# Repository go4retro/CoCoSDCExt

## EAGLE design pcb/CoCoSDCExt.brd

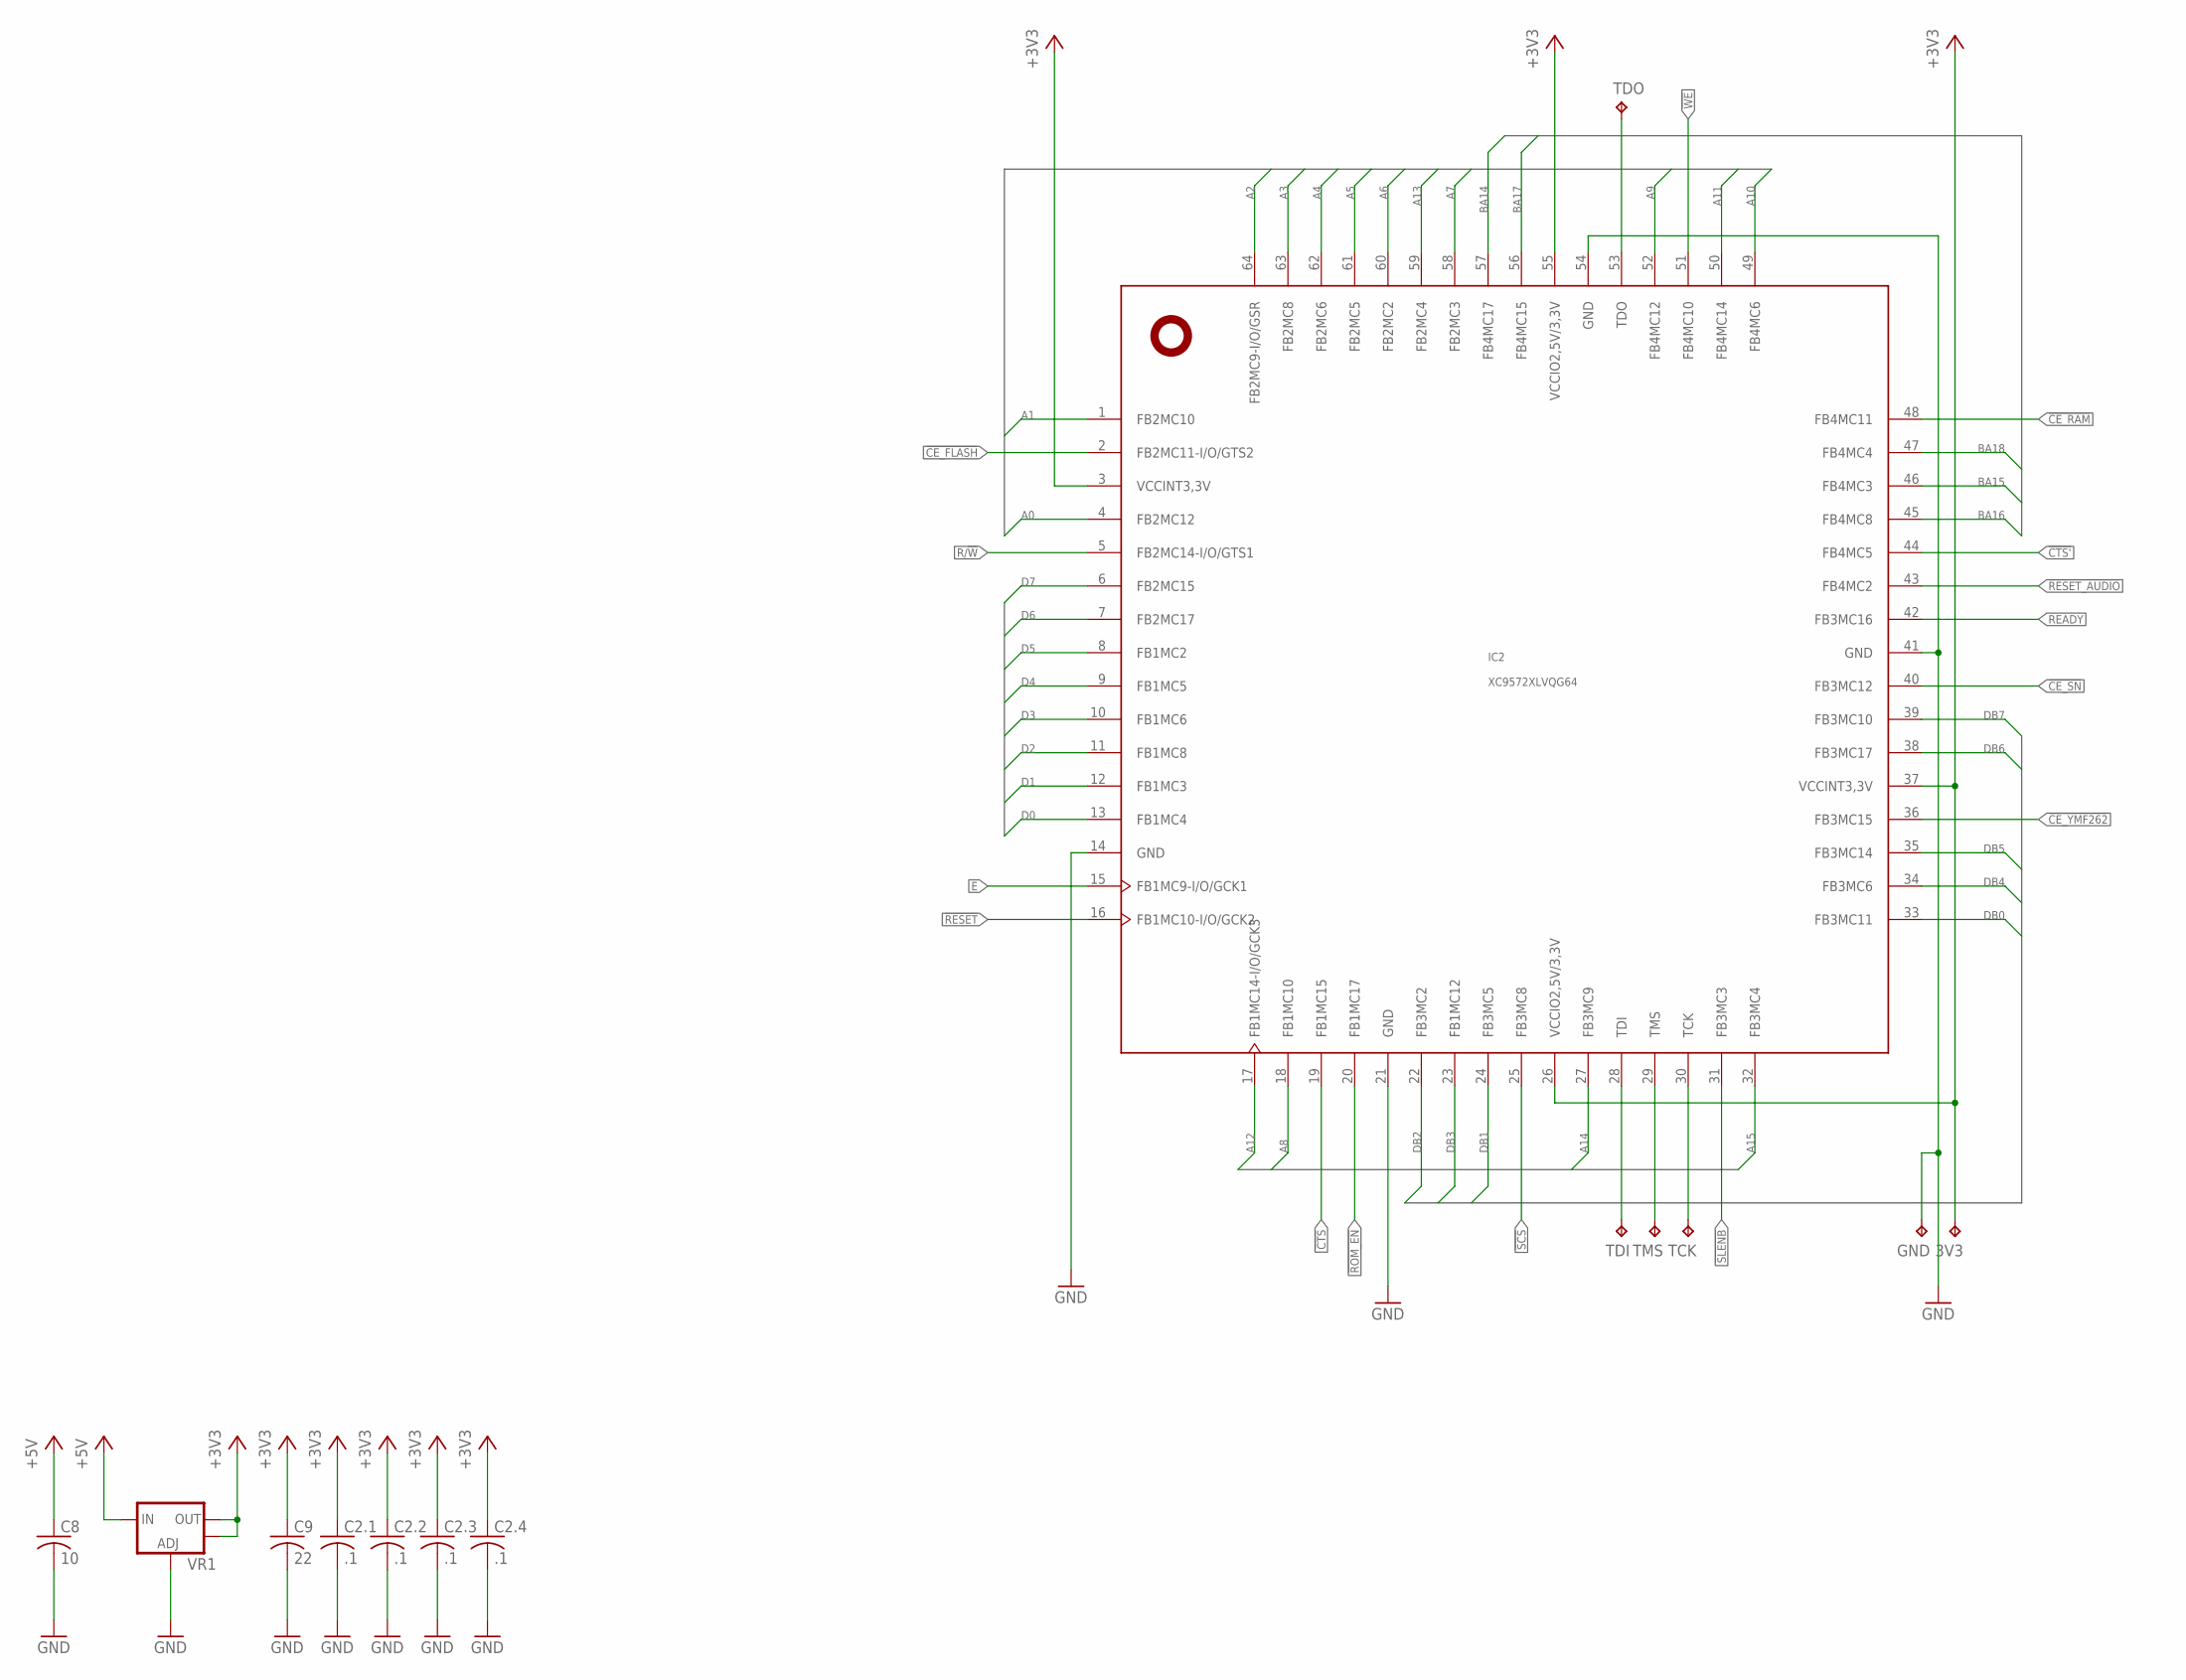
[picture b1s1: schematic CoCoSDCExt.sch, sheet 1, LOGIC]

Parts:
3V3: TPTP08R; TP08R
C2.1, C2.2, C2.3, C2.4: .1; C0402
C8: 10; C0805
C9: 22; C0805
GND: TPTP08R; TP08R
IC2: XC9572XLVQG64; VQFP64
TCK: TPTP08R; TP08R
TDI: TPTP08R; TP08R
TDO: TPTP08R; TP08R
TMS: TPTP08R; TP08R
VR1: V_REG_LM1117SOT223; SOT223

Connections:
!CE_FLASH: IC2.2 (FB2MC11-I/O/GTS2); also elsewhere on the board
!CE_RAM: IC2.48 (FB4MC11); also elsewhere on the board
!CE_SN: IC2.40 (FB3MC12); also elsewhere on the board
!CE_YMF262: IC2.36 (FB3MC15); also elsewhere on the board
!CTS: IC2.19 (FB1MC15); also elsewhere on the board
!CTS': IC2.44 (FB4MC5); also elsewhere on the board
!RESET: IC2.16 (FB1MC10-I/O/GCK2); also elsewhere on the board
!RESET_AUDIO: IC2.43 (FB4MC2); also elsewhere on the board
!ROM_EN: IC2.20 (FB1MC17); also elsewhere on the board
!SCS: IC2.25 (FB3MC8); also elsewhere on the board
!SLENB: IC2.31 (FB3MC3); also elsewhere on the board
!WE: IC2.51 (FB4MC10); also elsewhere on the board
+3V3: 3V3.TP, C2.1.1, C2.2.1, C2.3.1, C2.4.1, C9.1, IC2.3 (VCCINT3,3V), IC2.26 (VCCIO2,5V/3,3V), IC2.37 (VCCINT3,3V), IC2.55 (VCCIO2,5V/3,3V), VR1.2 (OUT), VR1.4 (OUT); also elsewhere on the board
+5V: C8.1, VR1.3 (IN); also elsewhere on the board
A0: IC2.4 (FB2MC12); also elsewhere on the board
A1: IC2.1 (FB2MC10); also elsewhere on the board
A2: IC2.64 (FB2MC9-I/O/GSR); also elsewhere on the board
A3: IC2.63 (FB2MC8); also elsewhere on the board
A4: IC2.62 (FB2MC6); also elsewhere on the board
A5: IC2.61 (FB2MC5); also elsewhere on the board
A6: IC2.60 (FB2MC2); also elsewhere on the board
A7: IC2.58 (FB2MC3); also elsewhere on the board
A8: IC2.18 (FB1MC10); also elsewhere on the board
A9: IC2.52 (FB4MC12); also elsewhere on the board
A10: IC2.49 (FB4MC6); also elsewhere on the board
A11: IC2.50 (FB4MC14); also elsewhere on the board
A12: IC2.17 (FB1MC14-I/O/GCK3); also elsewhere on the board
A13: IC2.59 (FB2MC4); also elsewhere on the board
A14: IC2.27 (FB3MC9); also elsewhere on the board
A15: IC2.32 (FB3MC4); also elsewhere on the board
BA14: IC2.57 (FB4MC17); also elsewhere on the board
BA15: IC2.46 (FB4MC3); also elsewhere on the board
BA16: IC2.45 (FB4MC8); also elsewhere on the board
BA17: IC2.56 (FB4MC15); also elsewhere on the board
BA18: IC2.47 (FB4MC4); also elsewhere on the board
D0: IC2.13 (FB1MC4); also elsewhere on the board
D1: IC2.12 (FB1MC3); also elsewhere on the board
D2: IC2.11 (FB1MC8); also elsewhere on the board
D3: IC2.10 (FB1MC6); also elsewhere on the board
D4: IC2.9 (FB1MC5); also elsewhere on the board
D5: IC2.8 (FB1MC2); also elsewhere on the board
D6: IC2.7 (FB2MC17); also elsewhere on the board
D7: IC2.6 (FB2MC15); also elsewhere on the board
DB0: IC2.33 (FB3MC11); also elsewhere on the board
DB1: IC2.24 (FB3MC5); also elsewhere on the board
DB2: IC2.22 (FB3MC2); also elsewhere on the board
DB3: IC2.23 (FB1MC12); also elsewhere on the board
DB4: IC2.34 (FB3MC6); also elsewhere on the board
DB5: IC2.35 (FB3MC14); also elsewhere on the board
DB6: IC2.38 (FB3MC17); also elsewhere on the board
DB7: IC2.39 (FB3MC10); also elsewhere on the board
E: IC2.15 (FB1MC9-I/O/GCK1); also elsewhere on the board
GND: C2.1.2, C2.2.2, C2.3.2, C2.4.2, C8.2, C9.2, GND.TP, IC2.14 (GND), IC2.21 (GND), IC2.41 (GND), IC2.54 (GND), VR1.1 (ADJ); also elsewhere on the board
R/!W: IC2.5 (FB2MC14-I/O/GTS1); also elsewhere on the board
READY: IC2.42 (FB3MC16); also elsewhere on the board
TCK: IC2.30 (TCK), TCK.TP
TDI: IC2.28 (TDI), TDI.TP
TDO: IC2.53 (TDO), TDO.TP
TMS: IC2.29 (TMS), TMS.TP

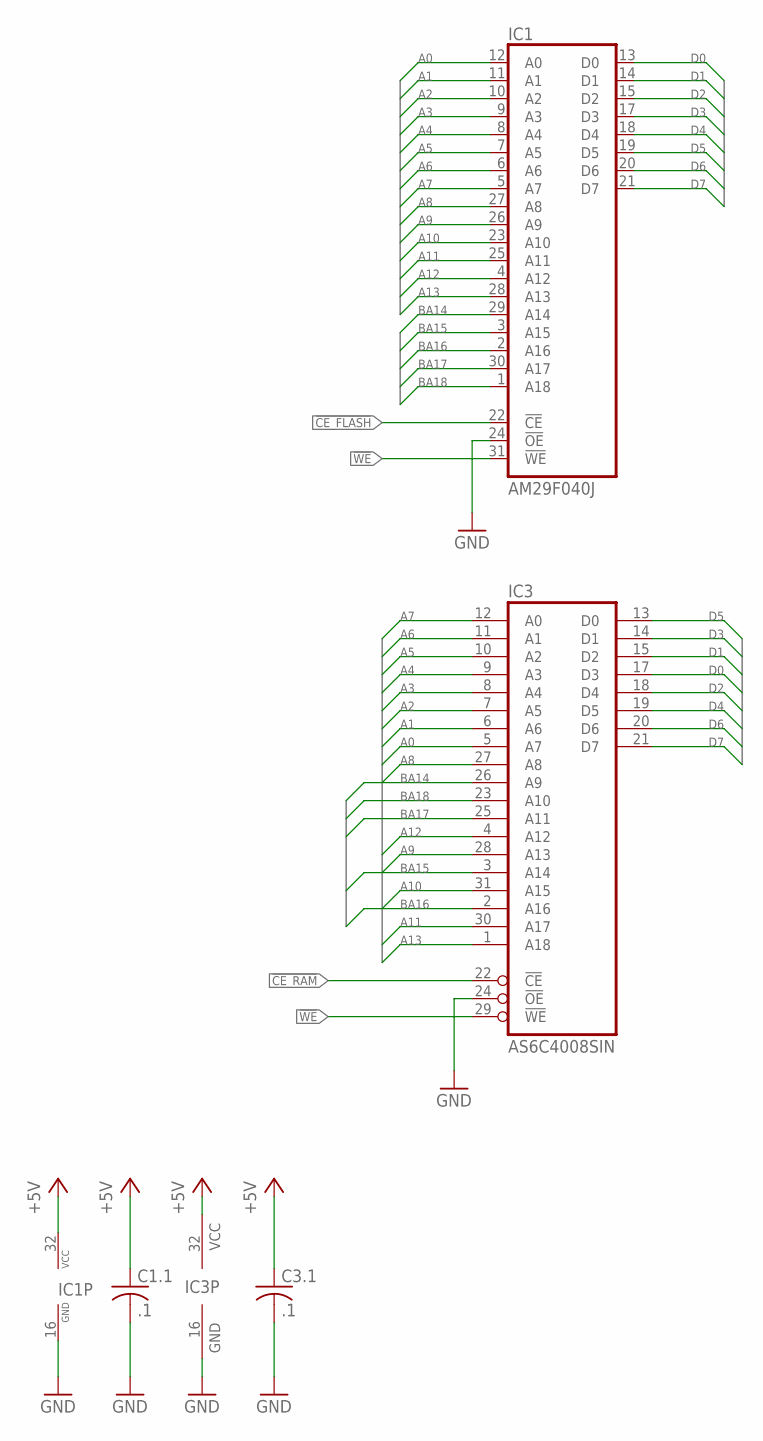
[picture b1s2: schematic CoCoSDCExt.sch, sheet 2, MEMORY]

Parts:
C1.1, C3.1: .1; C0402
IC1: AM29F040J; PLCC32R
IC3: AS6C4008SIN; SOP32L

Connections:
!CE_FLASH: IC1.22 (!CE); also elsewhere on the board
!CE_RAM: IC3.22 (!CE); also elsewhere on the board
!WE: IC1.31 (!WE), IC3.29 (!WE); also elsewhere on the board
+5V: C1.1.1, C3.1.1, IC1.32 (VCC), IC3.32 (VCC); also elsewhere on the board
A0: IC1.12 (A0), IC3.5 (A7); also elsewhere on the board
A1: IC1.11 (A1), IC3.6 (A6); also elsewhere on the board
A2: IC1.10 (A2), IC3.7 (A5); also elsewhere on the board
A3: IC1.9 (A3), IC3.8 (A4); also elsewhere on the board
A4: IC1.8 (A4), IC3.9 (A3); also elsewhere on the board
A5: IC1.7 (A5), IC3.10 (A2); also elsewhere on the board
A6: IC1.6 (A6), IC3.11 (A1); also elsewhere on the board
A7: IC1.5 (A7), IC3.12 (A0); also elsewhere on the board
A8: IC1.27 (A8), IC3.27 (A8); also elsewhere on the board
A9: IC1.26 (A9), IC3.28 (A13); also elsewhere on the board
A10: IC1.23 (A10), IC3.31 (A15); also elsewhere on the board
A11: IC1.25 (A11), IC3.30 (A17); also elsewhere on the board
A12: IC1.4 (A12), IC3.4 (A12); also elsewhere on the board
A13: IC1.28 (A13), IC3.1 (A18); also elsewhere on the board
BA14: IC1.29 (A14), IC3.26 (A9); also elsewhere on the board
BA15: IC1.3 (A15), IC3.3 (A14); also elsewhere on the board
BA16: IC1.2 (A16), IC3.2 (A16); also elsewhere on the board
BA17: IC1.30 (A17), IC3.25 (A11); also elsewhere on the board
BA18: IC1.1 (A18), IC3.23 (A10); also elsewhere on the board
D0: IC1.13 (D0), IC3.17 (D3); also elsewhere on the board
D1: IC1.14 (D1), IC3.15 (D2); also elsewhere on the board
D2: IC1.15 (D2), IC3.18 (D4); also elsewhere on the board
D3: IC1.17 (D3), IC3.14 (D1); also elsewhere on the board
D4: IC1.18 (D4), IC3.19 (D5); also elsewhere on the board
D5: IC1.19 (D5), IC3.13 (D0); also elsewhere on the board
D6: IC1.20 (D6), IC3.20 (D6); also elsewhere on the board
D7: IC1.21 (D7), IC3.21 (D7); also elsewhere on the board
GND: C1.1.2, C3.1.2, IC1.16 (GND), IC1.24 (!OE), IC3.16 (GND), IC3.24 (!OE); also elsewhere on the board

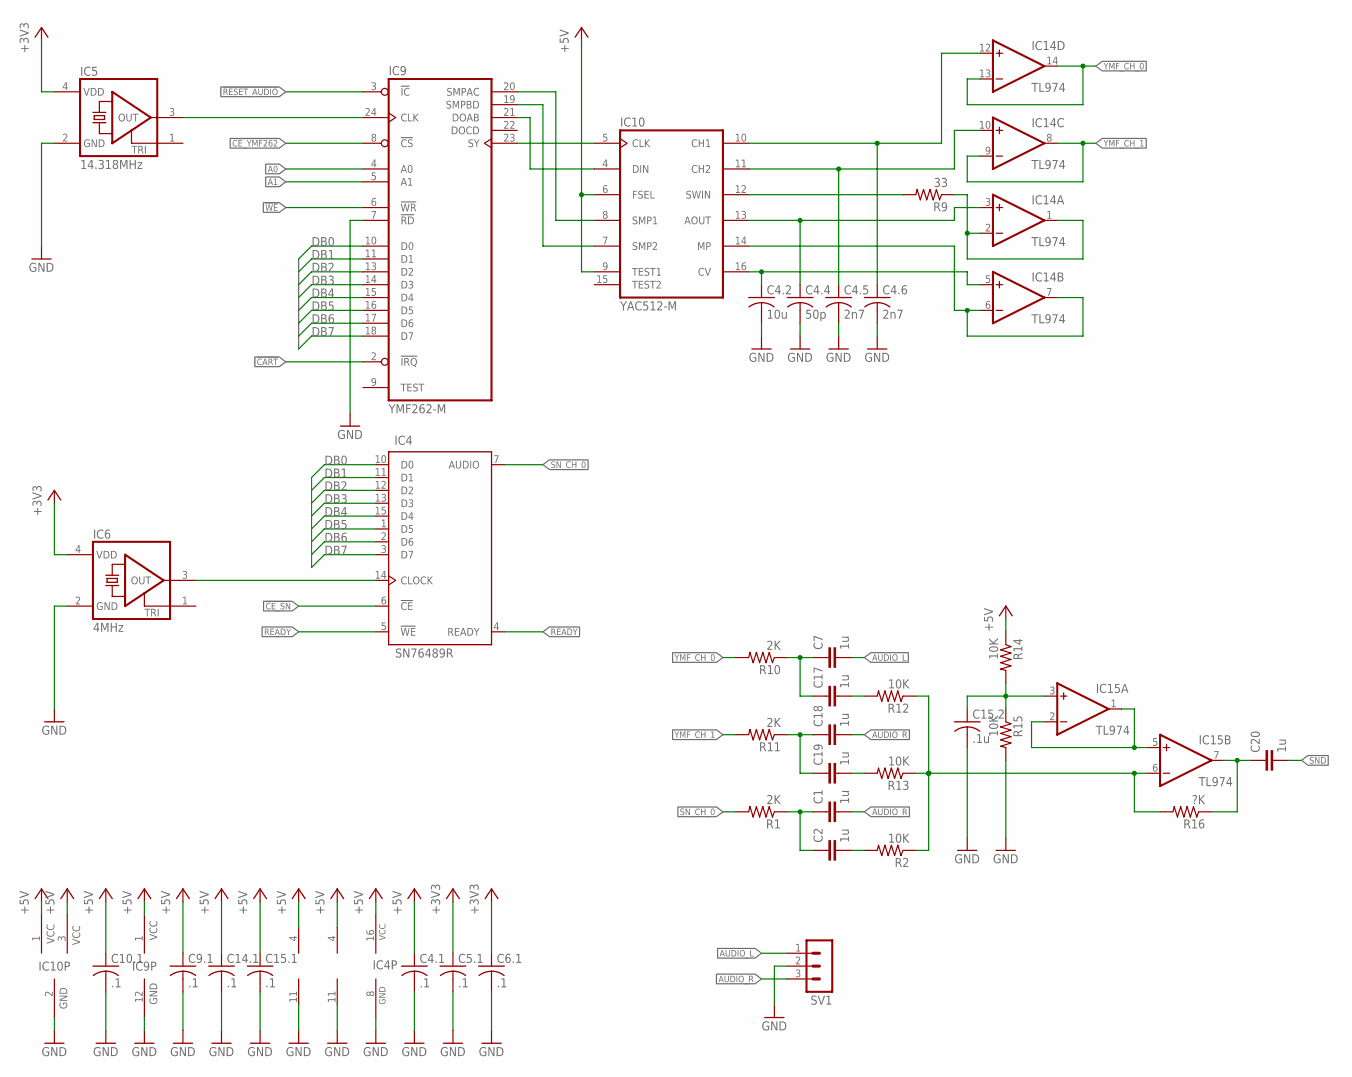
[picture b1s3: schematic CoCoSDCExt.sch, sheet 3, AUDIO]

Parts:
C1, C2, C7, C17, C18, C19, C20: 1u; SV-B
C4.1, C5.1, C6.1, C9.1, C10.1, C14.1, C15.1: .1; C0402
C4.2: 10u; C0805
C4.4: 50p; C0402
C4.5, C4.6: 2n7; C0402
C15.2: .1u; C0402
IC4: SN76489R; DIL16-RP
IC5: 14.318MHz; ASE
IC6: 4MHz; ASE
IC9: YMF262-M; SO24W
IC10: YAC512-M; SO16
IC14, IC15: TL974; TSSOP14
R1, R10, R11: 2K; R1206
R2, R12, R13: 10K; R1206
R9: 33; R0402
R14, R15: 10K; R0402
R16: ?K; R1206
SV1: MA03-1

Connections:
!CART: IC9.2 (!IRQ); also elsewhere on the board
!CE_SN: IC4.6 (!CE); also elsewhere on the board
!CE_YMF262: IC9.8 (!CS); also elsewhere on the board
!RESET_AUDIO: IC9.3 (!IC); also elsewhere on the board
!WE: IC9.6 (!WR); also elsewhere on the board
+3V3: C5.1.1, C6.1.1, IC5.4 (VDD), IC6.4 (VDD); also elsewhere on the board
+5V: C4.1.1, C9.1.1, C10.1.1, C14.1.1, C15.1.1, IC4.16 (VCC), IC9.1 (VCC), IC10.1 (VCC), IC10.3 (VCC), IC10.6 (FSEL), IC10.9 (TEST1), IC14.4 (V+), IC15.4 (V+), R14.1; also elsewhere on the board
A0: IC9.4 (A0); also elsewhere on the board
A1: IC9.5 (A1); also elsewhere on the board
AUDIO_L: C7.+ (1), SV1.1
AUDIO_R: C1.+ (1), C18.+ (1), SV1.3
DB0: IC4.10 (D0), IC9.10 (D0); also elsewhere on the board
DB1: IC4.11 (D1), IC9.11 (D1); also elsewhere on the board
DB2: IC4.12 (D2), IC9.13 (D2); also elsewhere on the board
DB3: IC4.13 (D3), IC9.14 (D3); also elsewhere on the board
DB4: IC4.15 (D4), IC9.15 (D4); also elsewhere on the board
DB5: IC4.1 (D5), IC9.16 (D5); also elsewhere on the board
DB6: IC4.2 (D6), IC9.17 (D6); also elsewhere on the board
DB7: IC4.3 (D7), IC9.18 (D7); also elsewhere on the board
GND: C4.1.2, C4.2.2, C4.4.2, C4.5.2, C4.6.2, C5.1.2, C6.1.2, C9.1.2, C10.1.2, C14.1.2, C15.1.2, C15.2.2, IC4.8 (GND), IC5.2 (GND), IC6.2 (GND), IC9.7 (!RD), IC9.12 (GND), IC10.2 (GND), IC14.11 (V-), IC15.11 (V-), R15.2, SV1.2; also elsewhere on the board
unnamed: IC4.14 (CLOCK), IC6.3 (OUT)
unnamed: C1.- (2), C2.- (2), R1.1
unnamed: C2.+ (1), R2.2
unnamed: IC9.23 (SY), IC10.5 (CLK)
unnamed: IC9.21 (DOAB), IC10.4 (DIN)
unnamed: C7.- (2), C17.- (2), R10.1
unnamed: IC9.20 (SMPAC), IC10.8 (SMP1)
unnamed: IC9.19 (SMPBD), IC10.7 (SMP2)
unnamed: IC5.3 (OUT), IC9.24 (CLK)
unnamed: C18.- (2), C19.- (2), R11.1
unnamed: IC10.12 (SWIN), R9.2
unnamed: C17.+ (1), R12.2
unnamed: C19.+ (1), R13.2
unnamed: IC15.6 (-IN), R2.1, R12.1, R13.1, R16.2
unnamed: IC14.1 (OUT), IC14.2 (-IN), R9.1
unnamed: C4.6.1, IC10.10 (CH1), IC14.12 (+IN)
unnamed: C4.5.1, IC10.11 (CH2), IC14.10 (+IN)
unnamed: IC15.1 (OUT), IC15.2 (-IN), IC15.5 (+IN)
unnamed: C4.4.1, IC10.13 (AOUT), IC14.3 (+IN)
unnamed: C15.2.1, IC15.3 (+IN), R14.2, R15.1
unnamed: IC10.14 (MP), IC14.6 (-IN), IC14.7 (OUT)
unnamed: C20.- (2), IC15.7 (OUT), R16.1
unnamed: C4.2.1, IC10.16 (CV), IC14.5 (+IN)
READY: IC4.4 (READY), IC4.5 (!WE); also elsewhere on the board
SND: C20.+ (1); also elsewhere on the board
SN_CH_0: IC4.7 (AUDIO), R1.2
YMF_CH_0: IC14.13 (-IN), IC14.14 (OUT), R10.2
YMF_CH_1: IC14.8 (OUT), IC14.9 (-IN), R11.2

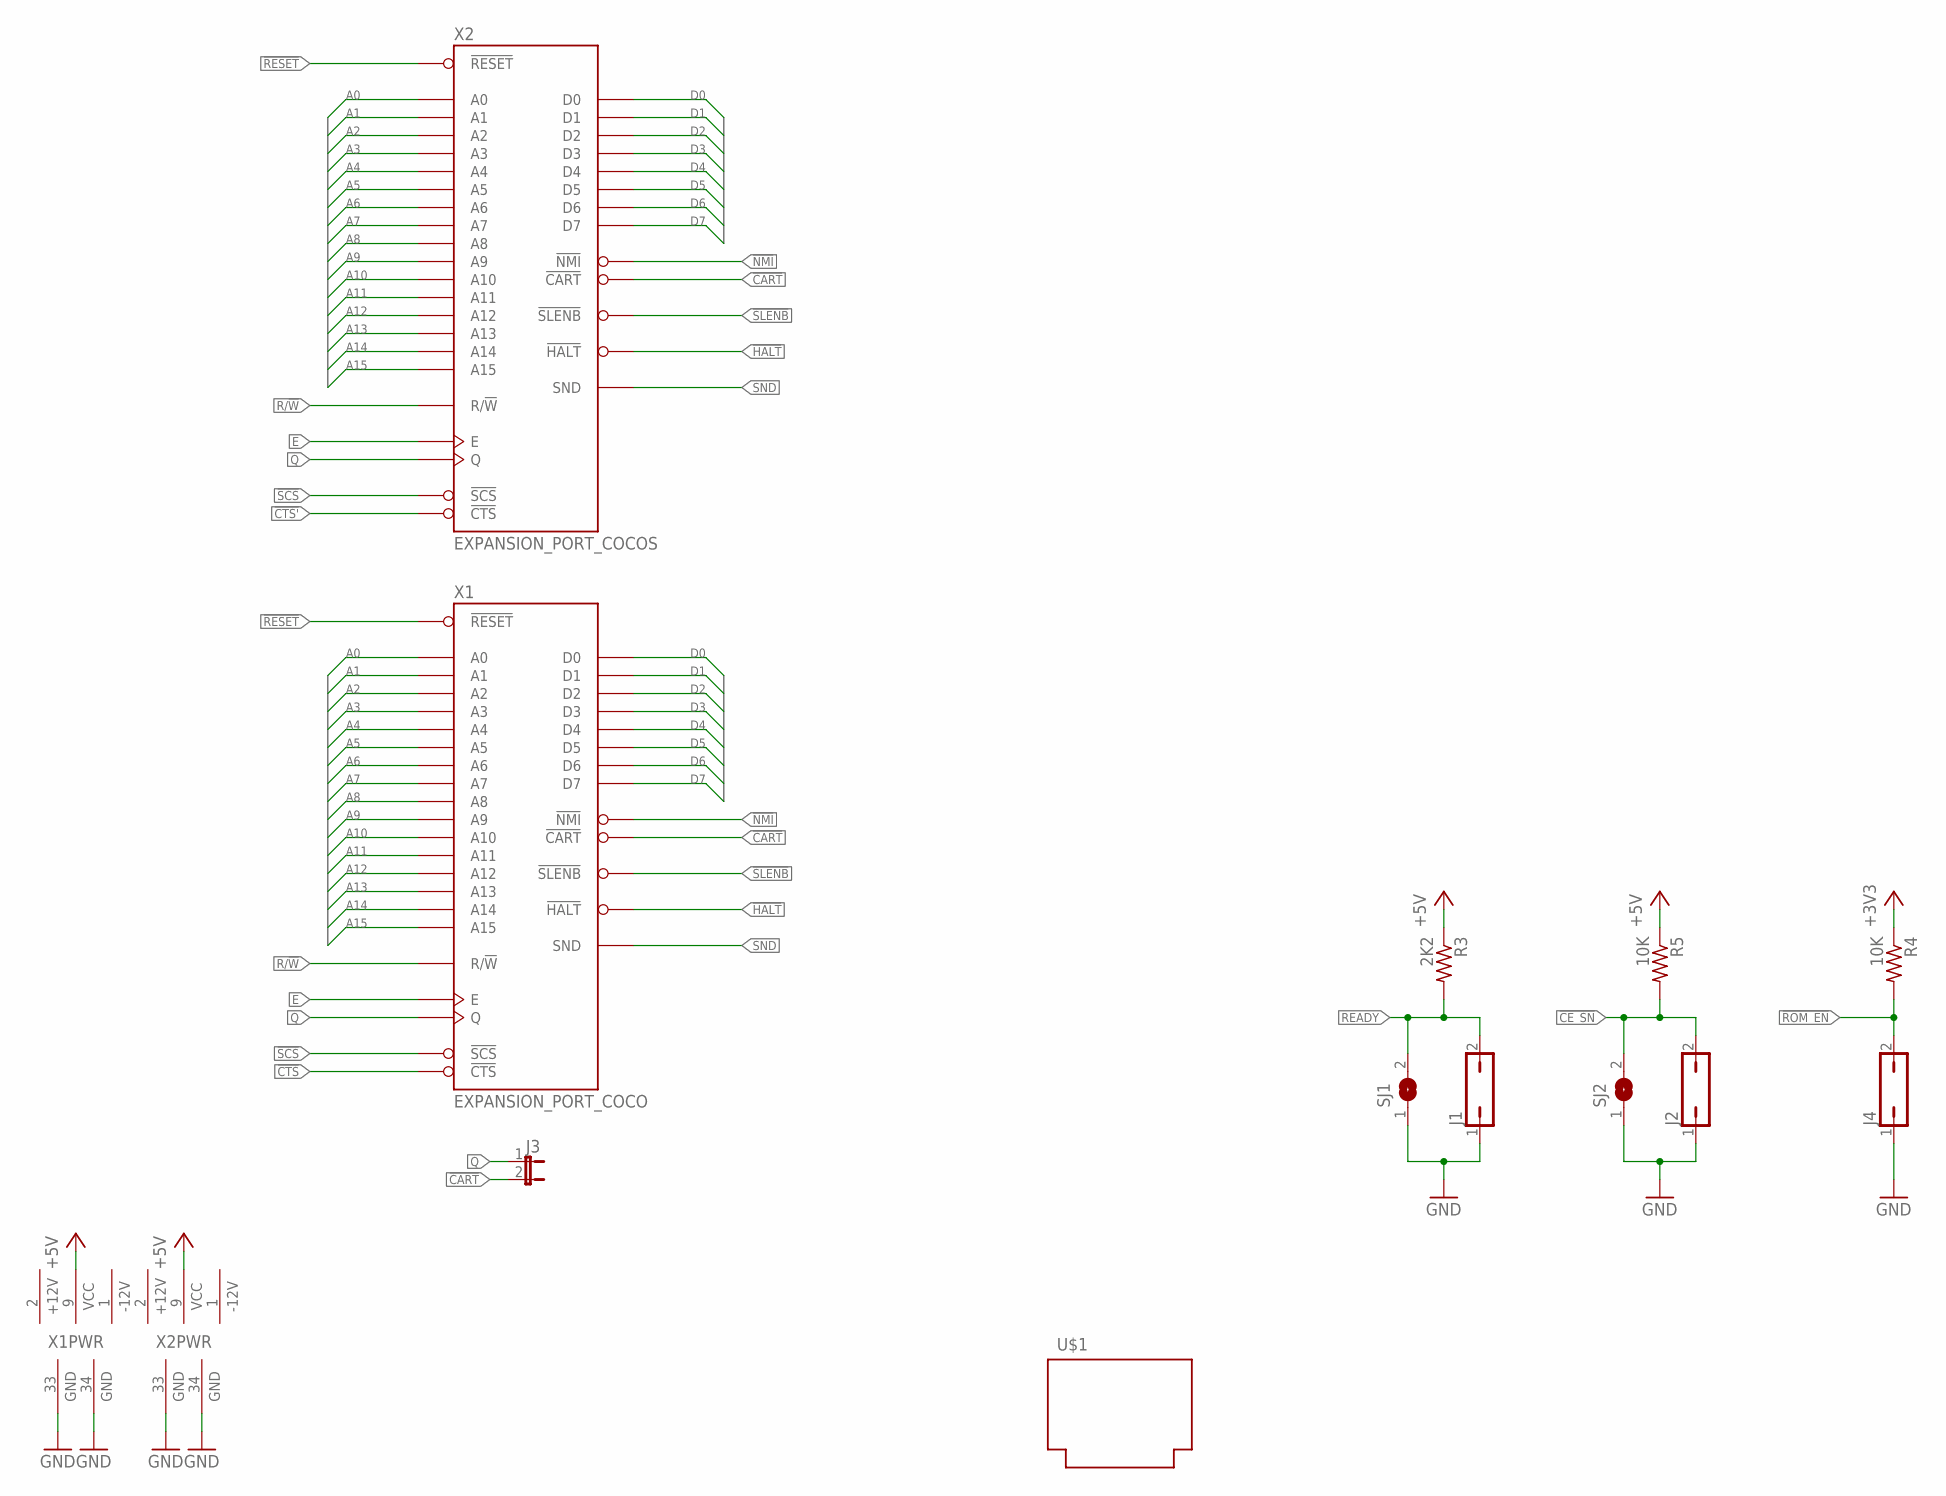
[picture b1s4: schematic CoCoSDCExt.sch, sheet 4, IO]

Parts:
J1, J2, J4: JP1Q; JP1
J3: JP1E; JP1
R3: 2K2; R0402
R4, R5: 10K; R0402
SJ1, SJ2: SJ
U$1: PROGRAM_PAK
X1: EXPANSION_PORT_COCO; MA20-2
X2: EXPANSION_PORT_COCOS; MA20-2_SHORT

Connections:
!CART: J3.2, X1.8 (!CART), X2.8 (!CART); also elsewhere on the board
!CE_SN: J2.2, R5.2, SJ2.2; also elsewhere on the board
!CTS: X1.32 (!CTS); also elsewhere on the board
!CTS': X2.32 (!CTS); also elsewhere on the board
!HALT: X1.3 (!HALT), X2.3 (!HALT)
!NMI: X1.4 (!NMI), X2.4 (!NMI)
!RESET: X1.5 (!RESET), X2.5 (!RESET); also elsewhere on the board
!ROM_EN: J4.2, R4.2; also elsewhere on the board
!SCS: X1.36 (!SCS), X2.36 (!SCS); also elsewhere on the board
!SLENB: X1.40 (!SLENB), X2.40 (!SLENB); also elsewhere on the board
+3V3: R4.1; also elsewhere on the board
+5V: R3.1, R5.1, X1.9 (VCC), X2.9 (VCC); also elsewhere on the board
+12V: X1.2 (+12V), X2.2 (+12V)
-12V: X1.1 (-12V), X2.1 (-12V)
A0: X1.19 (A0), X2.19 (A0); also elsewhere on the board
A1: X1.20 (A1), X2.20 (A1); also elsewhere on the board
A2: X1.21 (A2), X2.21 (A2); also elsewhere on the board
A3: X1.22 (A3), X2.22 (A3); also elsewhere on the board
A4: X1.23 (A4), X2.23 (A4); also elsewhere on the board
A5: X1.24 (A5), X2.24 (A5); also elsewhere on the board
A6: X1.25 (A6), X2.25 (A6); also elsewhere on the board
A7: X1.26 (A7), X2.26 (A7); also elsewhere on the board
A8: X1.27 (A8), X2.27 (A8); also elsewhere on the board
A9: X1.28 (A9), X2.28 (A9); also elsewhere on the board
A10: X1.29 (A10), X2.29 (A10); also elsewhere on the board
A11: X1.30 (A11), X2.30 (A11); also elsewhere on the board
A12: X1.31 (A12), X2.31 (A12); also elsewhere on the board
A13: X1.37 (A13), X2.37 (A13); also elsewhere on the board
A14: X1.38 (A14), X2.38 (A14); also elsewhere on the board
A15: X1.39 (A15), X2.39 (A15); also elsewhere on the board
D0: X1.10 (D0), X2.10 (D0); also elsewhere on the board
D1: X1.11 (D1), X2.11 (D1); also elsewhere on the board
D2: X1.12 (D2), X2.12 (D2); also elsewhere on the board
D3: X1.13 (D3), X2.13 (D3); also elsewhere on the board
D4: X1.14 (D4), X2.14 (D4); also elsewhere on the board
D5: X1.15 (D5), X2.15 (D5); also elsewhere on the board
D6: X1.16 (D6), X2.16 (D6); also elsewhere on the board
D7: X1.17 (D7), X2.17 (D7); also elsewhere on the board
E: X1.6 (E), X2.6 (E); also elsewhere on the board
GND: J1.1, J2.1, J4.1, SJ1.1, SJ2.1, X1.33 (GND), X1.34 (GND), X2.33 (GND), X2.34 (GND); also elsewhere on the board
Q: J3.1, X1.7 (Q), X2.7 (Q)
R/!W: X1.18 (R/!W), X2.18 (R/!W); also elsewhere on the board
READY: J1.2, R3.2, SJ1.2; also elsewhere on the board
SND: X1.35 (SND), X2.35 (SND); also elsewhere on the board

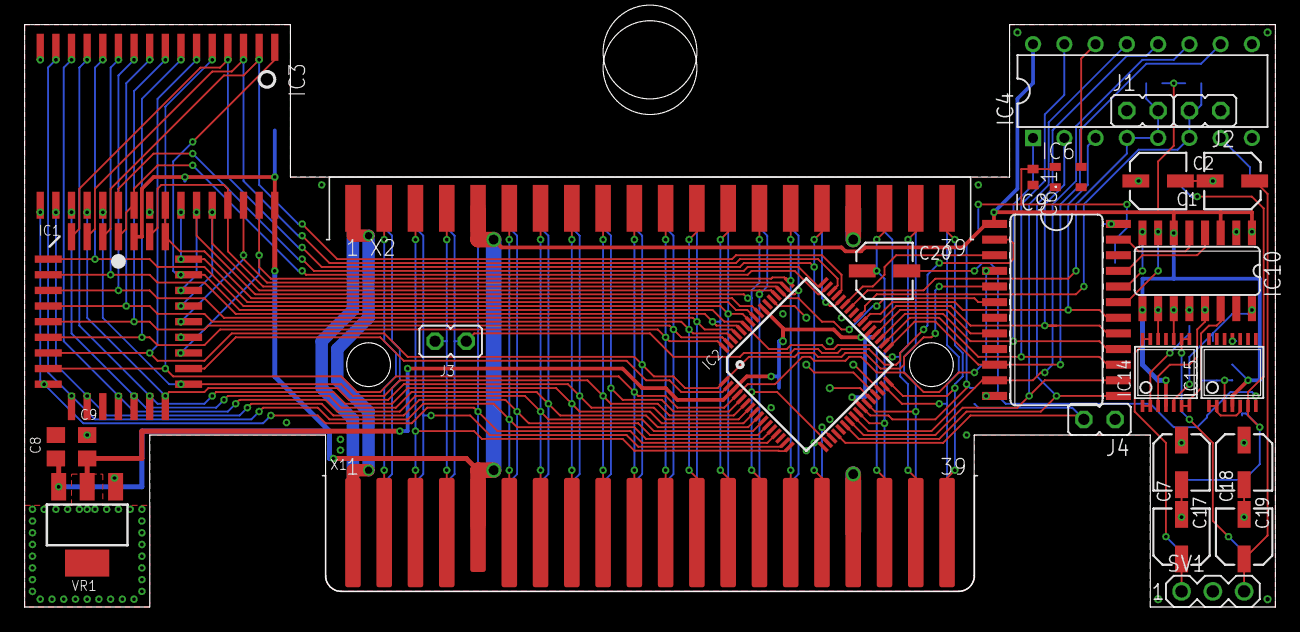
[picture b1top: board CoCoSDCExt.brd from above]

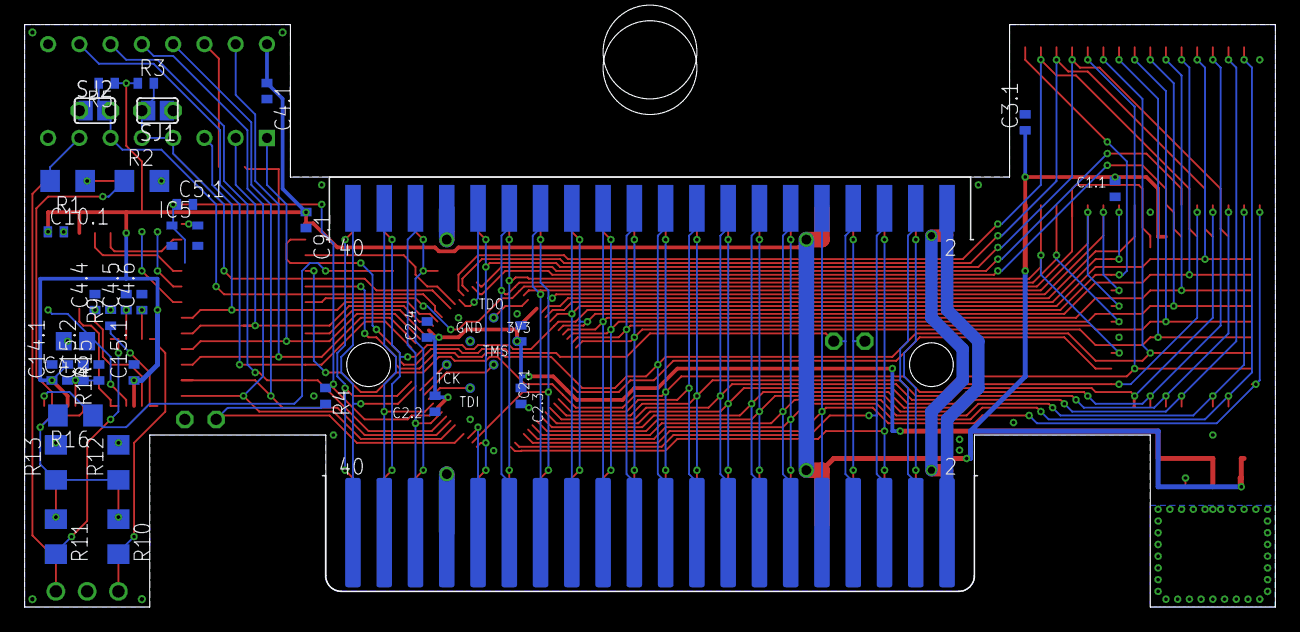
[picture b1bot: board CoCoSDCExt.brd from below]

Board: 2 copper layers, 101.6 x 47.3 mm, 67 parts (39 on the bottom side), 94 nets.

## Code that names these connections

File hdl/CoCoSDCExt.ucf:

#PACE: Start of Constraints generated by PACE

#PACE: Start of PACE I/O Pin Assignments
NET "_ce_flash"  LOC = "P2"  ;
NET "_ce_sram"  LOC = "P48"  ;
NET "_ce_ymf"  LOC = "P36"  ;
NET "_cts"  LOC = "P19"  ;
NET "_cts_out"  LOC = "P44"  ;
NET "_reset"  LOC = "P16"  ;
NET "_reset_audio"  LOC = "P43"  ;
NET "_rom_enable"  LOC = "P20"  ;
NET "_scs"  LOC = "P25"  ;
NET "_slenb"  LOC = "P31"  ;
NET "_we"  LOC = "P51"  ;
NET "address<0>"  LOC = "P4"  ;
NET "address<10>"  LOC = "P49"  ;
NET "address<11>"  LOC = "P50"  ;
NET "address<12>"  LOC = "P17"  ;
NET "address<13>"  LOC = "P59"  ;
NET "address<14>"  LOC = "P27"  ;
NET "address<15>"  LOC = "P32"  ;
NET "address<1>"  LOC = "P1"  ;
NET "address<2>"  LOC = "P64"  ;
NET "address<3>"  LOC = "P63"  ;
NET "address<4>"  LOC = "P62"  ;
NET "address<5>"  LOC = "P61"  ;
NET "address<6>"  LOC = "P60"  ;
NET "address<7>"  LOC = "P58"  ;
NET "address<8>"  LOC = "P18"  ;
NET "address<9>"  LOC = "P52"  ;
NET "baddress<14>"  LOC = "P57"  ;
NET "baddress<15>"  LOC = "P46"  ;
NET "baddress<16>"  LOC = "P45"  ;
NET "baddress<17>"  LOC = "P56"  ;
NET "baddress<18>"  LOC = "P47"  ;
NET "bdata<0>"  LOC = "P33"  ;
NET "bdata<1>"  LOC = "P24"  ;
NET "bdata<2>"  LOC = "P22"  ;
NET "bdata<3>"  LOC = "P23"  ;
NET "bdata<4>"  LOC = "P34"  ;
NET "bdata<5>"  LOC = "P35"  ;
NET "bdata<6>"  LOC = "P38"  ;
NET "bdata<7>"  LOC = "P39"  ;
NET "clock"  LOC = "P15"  ;
NET "data<0>"  LOC = "P13"  ;
NET "data<1>"  LOC = "P12"  ;
NET "data<2>"  LOC = "P11"  ;
NET "data<3>"  LOC = "P10"  ;
NET "data<4>"  LOC = "P9"  ;
NET "data<5>"  LOC = "P8"  ;
NET "data<6>"  LOC = "P7"  ;
NET "data<7>"  LOC = "P6"  ;
NET "r_w"  LOC = "P5"  ;

#PACE: Start of PACE Area Constraints

#PACE: Start of PACE Prohibit Constraints

#PACE: End of Constraints generated by PACE

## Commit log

2018-12-05 Add in YMF-262 audio IC
2018-12-05 Initial fitment
2018-12-05 More fitment positioning
2018-12-05 Decision to use tabs below PCB for filters
2018-12-05 positioning
2018-12-05 Extending PCB to support tabs
2018-12-05 routing pass-thru connector
2018-12-05 Routing address lines for flash/ram
2018-12-05 nearly routed
2018-12-05 fully routed
2018-12-05 Added SN76489AN
2018-12-05 More fixes
2018-12-05 Fixed SN signalling
2018-12-05 Optimized SN signalling and reduced parts count
2018-12-07 Initial HDL
2018-12-07 Ignore temp files
2019-02-09 Added UCF file and Verilog tweaks

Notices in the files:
parts and their libraries:
SparkFun: Licensing: CC v3.0 Share-Alike You are welcome to use this library for commercial purposes.
cap-pan40: Copyright (C) 2004, Bob Starr
